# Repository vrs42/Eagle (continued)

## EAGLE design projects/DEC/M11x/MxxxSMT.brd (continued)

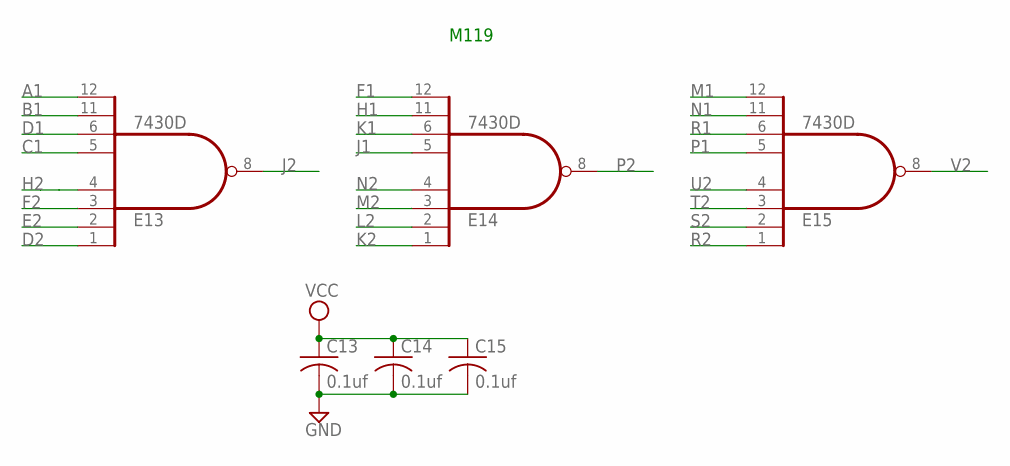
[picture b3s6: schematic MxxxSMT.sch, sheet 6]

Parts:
C13, C14, C15: 0.1uf; C050-025X075
E13, E14, E15: 7430D; SO14

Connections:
A1: E13.12 (I7); also elsewhere on the board
B1: E13.11 (I6); also elsewhere on the board
C1: E13.5 (I4); also elsewhere on the board
D1: E13.6 (I5); also elsewhere on the board
D2: E13.1 (I0); also elsewhere on the board
E2: E13.2 (I1); also elsewhere on the board
F1: E14.12 (I7); also elsewhere on the board
F2: E13.3 (I2); also elsewhere on the board
GND: C13.2, C14.2, C15.2, E13.7 (GND), E14.7 (GND), E15.7 (GND); also elsewhere on the board
H1: E14.11 (I6); also elsewhere on the board
H2: E13.4 (I3); also elsewhere on the board
J1: E14.5 (I4); also elsewhere on the board
J2: E13.8 (O); also elsewhere on the board
K1: E14.6 (I5); also elsewhere on the board
K2: E14.1 (I0); also elsewhere on the board
L2: E14.2 (I1); also elsewhere on the board
M1: E15.12 (I7); also elsewhere on the board
M2: E14.3 (I2); also elsewhere on the board
N1: E15.11 (I6); also elsewhere on the board
N2: E14.4 (I3); also elsewhere on the board
P1: E15.5 (I4); also elsewhere on the board
P2: E14.8 (O); also elsewhere on the board
R1: E15.6 (I5); also elsewhere on the board
R2: E15.1 (I0); also elsewhere on the board
S2: E15.2 (I1); also elsewhere on the board
T2: E15.3 (I2); also elsewhere on the board
U2: E15.4 (I3); also elsewhere on the board
V2: E15.8 (O); also elsewhere on the board
VCC: C13.1, C14.1, C15.1, E13.14 (VCC), E14.14 (VCC), E15.14 (VCC); also elsewhere on the board

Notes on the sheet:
M119

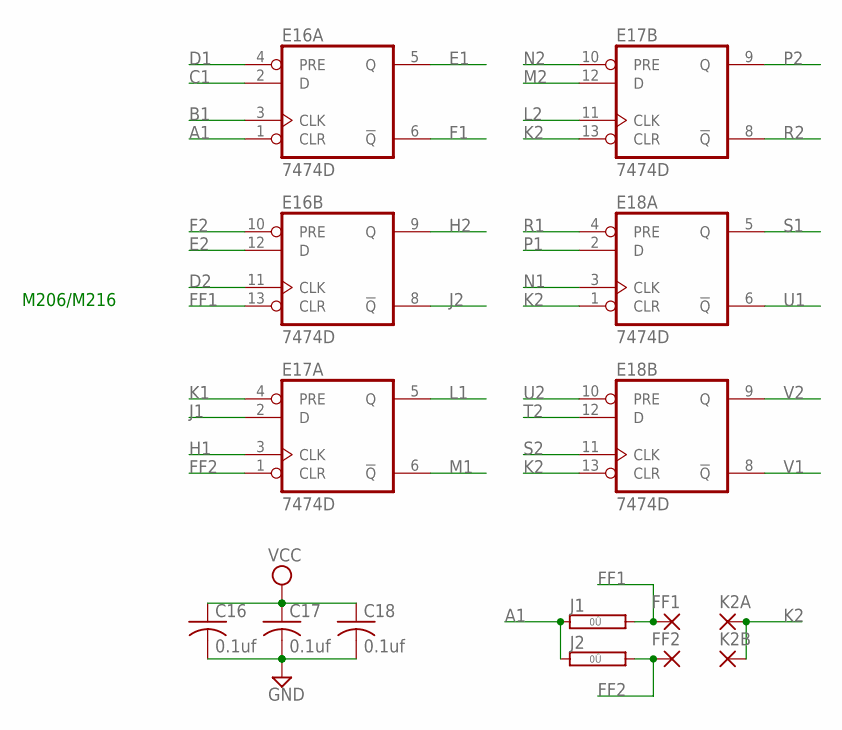
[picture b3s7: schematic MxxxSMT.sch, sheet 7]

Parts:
C16, C17, C18: 0.1uf; C050-025X075
E16, E17, E18: 7474D; SO14
FF1, FF2: 1,6/0,8
J1, J2: 0R; 0R/10
K2A, K2B: 1,6/0,8

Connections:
A1: E16.1 (CLR), J1.1, J2.1; also elsewhere on the board
B1: E16.3 (CLK); also elsewhere on the board
C1: E16.2 (D); also elsewhere on the board
D1: E16.4 (PRE); also elsewhere on the board
D2: E16.11 (CLK); also elsewhere on the board
E1: E16.5 (Q); also elsewhere on the board
E2: E16.12 (D); also elsewhere on the board
F1: E16.6 (!Q); also elsewhere on the board
F2: E16.10 (PRE); also elsewhere on the board
FF1: E16.13 (CLR), FF1.1, J1.2; also elsewhere on the board
FF2: E17.1 (CLR), FF2.1, J2.2; also elsewhere on the board
GND: C16.2, C17.2, C18.2, E16.7 (GND), E17.7 (GND), E18.7 (GND); also elsewhere on the board
H1: E17.3 (CLK); also elsewhere on the board
H2: E16.9 (Q); also elsewhere on the board
J1: E17.2 (D); also elsewhere on the board
J2: E16.8 (!Q); also elsewhere on the board
K1: E17.4 (PRE); also elsewhere on the board
K2: E17.13 (CLR), E18.1 (CLR), E18.13 (CLR), K2A.1, K2B.1; also elsewhere on the board
L1: E17.5 (Q); also elsewhere on the board
L2: E17.11 (CLK); also elsewhere on the board
M1: E17.6 (!Q); also elsewhere on the board
M2: E17.12 (D); also elsewhere on the board
N1: E18.3 (CLK); also elsewhere on the board
N2: E17.10 (PRE); also elsewhere on the board
P1: E18.2 (D); also elsewhere on the board
P2: E17.9 (Q); also elsewhere on the board
R1: E18.4 (PRE); also elsewhere on the board
R2: E17.8 (!Q); also elsewhere on the board
S1: E18.5 (Q); also elsewhere on the board
S2: E18.11 (CLK); also elsewhere on the board
T2: E18.12 (D); also elsewhere on the board
U1: E18.6 (!Q); also elsewhere on the board
U2: E18.10 (PRE); also elsewhere on the board
V1: E18.8 (!Q); also elsewhere on the board
V2: E18.9 (Q); also elsewhere on the board
VCC: C16.1, C17.1, C18.1, E16.14 (VCC), E17.14 (VCC), E18.14 (VCC); also elsewhere on the board

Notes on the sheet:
M206/M216

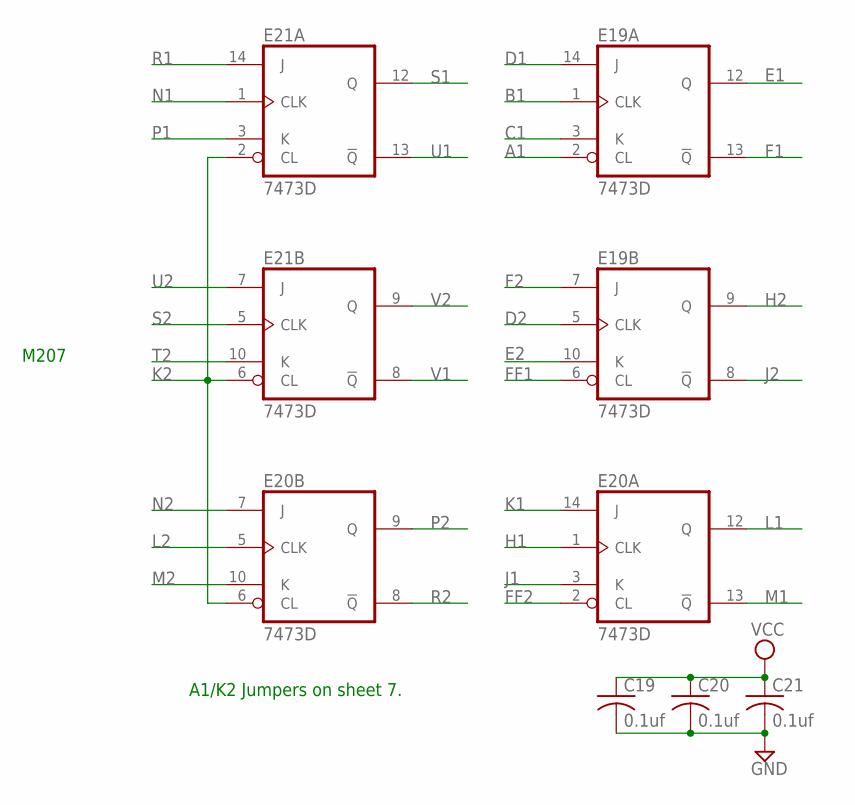
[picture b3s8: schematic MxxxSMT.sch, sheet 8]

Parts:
C19, C20, C21: 0.1uf; C050-025X075
E19, E20, E21: 7473D; SO14

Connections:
A1: E19.2 (CL); also elsewhere on the board
B1: E19.1 (CLK); also elsewhere on the board
C1: E19.3 (K); also elsewhere on the board
D1: E19.14 (J); also elsewhere on the board
D2: E19.5 (CLK); also elsewhere on the board
E1: E19.12 (Q); also elsewhere on the board
E2: E19.10 (K); also elsewhere on the board
F1: E19.13 (!Q); also elsewhere on the board
F2: E19.7 (J); also elsewhere on the board
FF1: E19.6 (CL); also elsewhere on the board
FF2: E20.2 (CL); also elsewhere on the board
GND: C19.2, C20.2, C21.2, E19.11 (GND), E20.11 (GND), E21.11 (GND); also elsewhere on the board
H1: E20.1 (CLK); also elsewhere on the board
H2: E19.9 (Q); also elsewhere on the board
J1: E20.3 (K); also elsewhere on the board
J2: E19.8 (!Q); also elsewhere on the board
K1: E20.14 (J); also elsewhere on the board
K2: E20.6 (CL), E21.2 (CL), E21.6 (CL); also elsewhere on the board
L1: E20.12 (Q); also elsewhere on the board
L2: E20.5 (CLK); also elsewhere on the board
M1: E20.13 (!Q); also elsewhere on the board
M2: E20.10 (K); also elsewhere on the board
N1: E21.1 (CLK); also elsewhere on the board
N2: E20.7 (J); also elsewhere on the board
P1: E21.3 (K); also elsewhere on the board
P2: E20.9 (Q); also elsewhere on the board
R1: E21.14 (J); also elsewhere on the board
R2: E20.8 (!Q); also elsewhere on the board
S1: E21.12 (Q); also elsewhere on the board
S2: E21.5 (CLK); also elsewhere on the board
T2: E21.10 (K); also elsewhere on the board
U1: E21.13 (!Q); also elsewhere on the board
U2: E21.7 (J); also elsewhere on the board
V1: E21.8 (!Q); also elsewhere on the board
V2: E21.9 (Q); also elsewhere on the board
VCC: C19.1, C20.1, C21.1, E19.4 (VCC), E20.4 (VCC), E21.4 (VCC); also elsewhere on the board

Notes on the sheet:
A1/K2 Jumpers on sheet 7.
M207

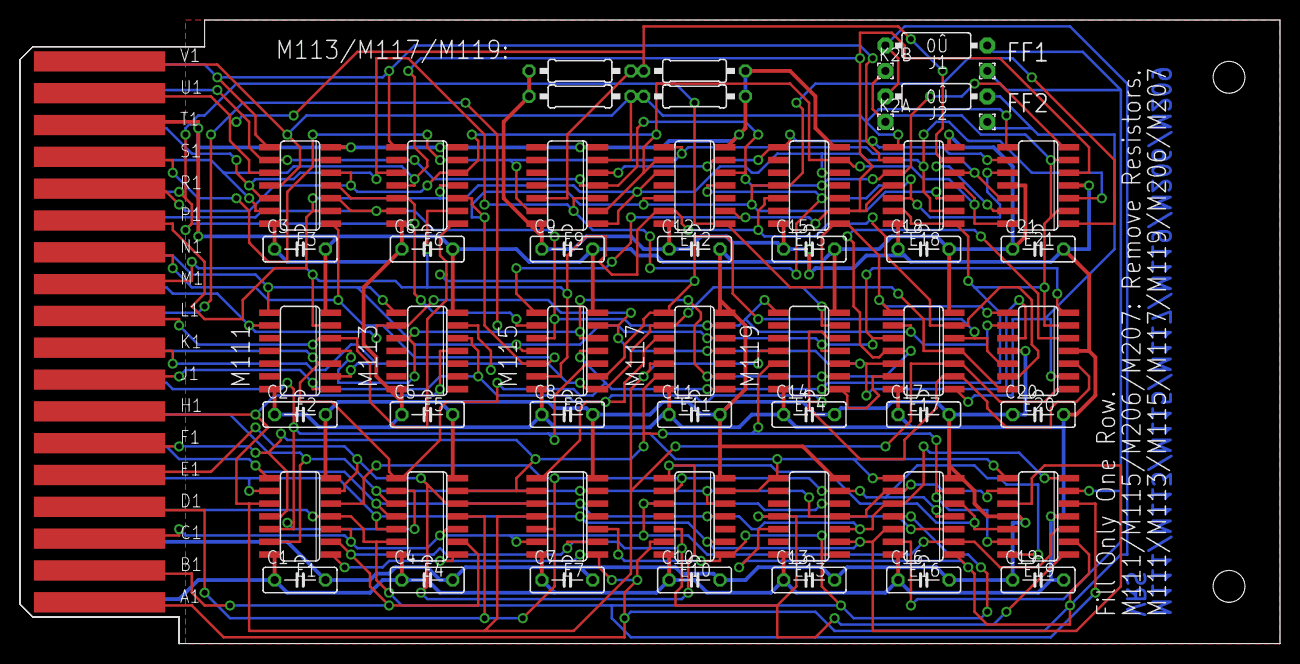
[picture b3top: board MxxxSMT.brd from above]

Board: 2 copper layers, 125.7 x 62.2 mm, 54 parts (0 on the bottom side), 36 nets.

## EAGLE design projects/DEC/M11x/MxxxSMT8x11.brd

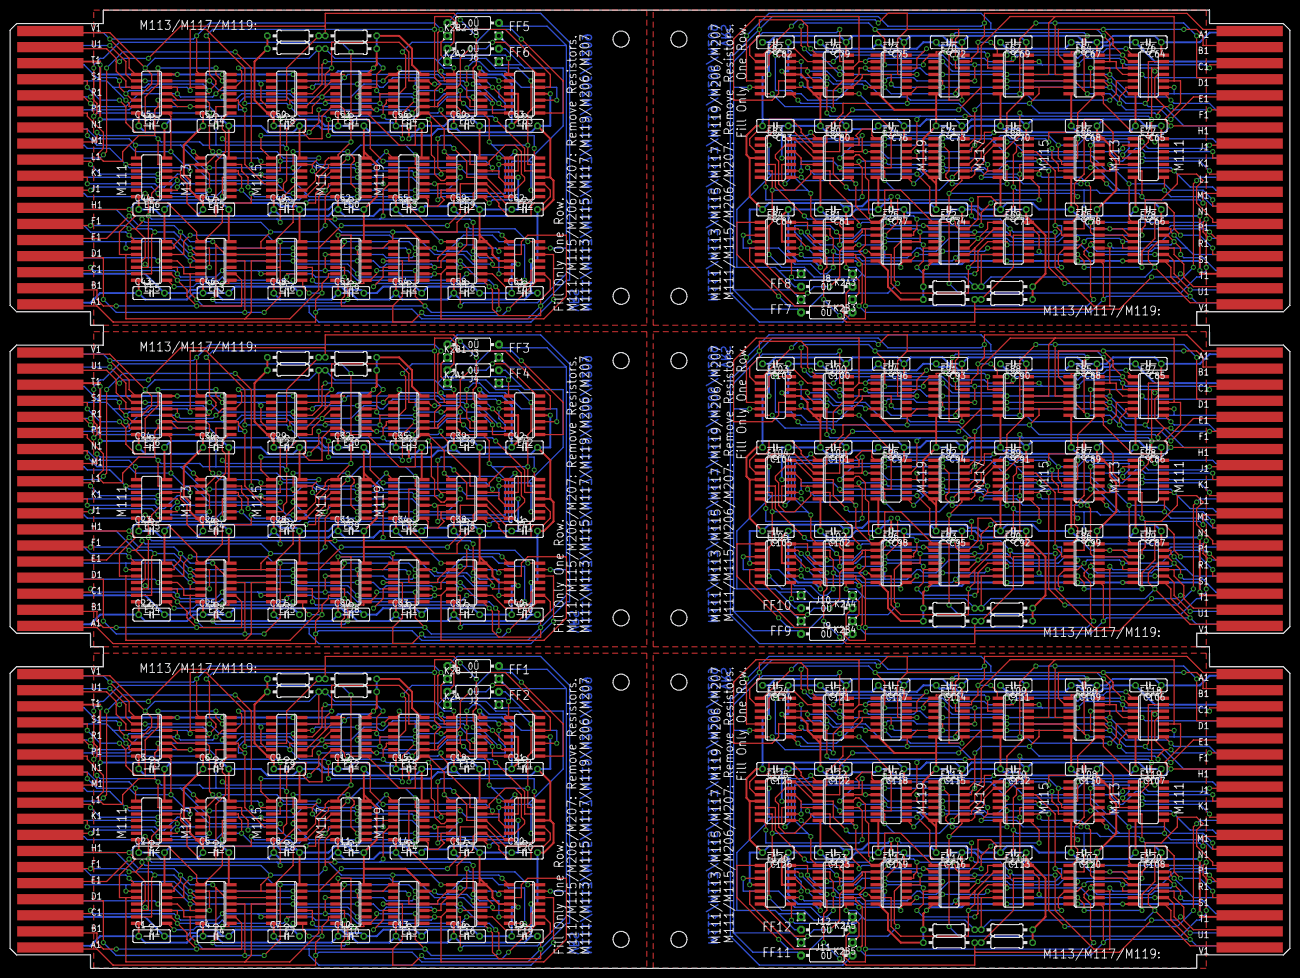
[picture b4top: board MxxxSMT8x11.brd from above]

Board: 2 copper layers, 252.7 x 189.2 mm, 318 parts (0 on the bottom side), 216 nets.

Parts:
C1, C2, C3, C4, C5, C6, C7, C8, C9, C10, C11, C12, C13, C14, C15, C16, C17, C18, C19, C20, C21, C22, C23, C24, C25, C26, C27, C28, C29, C30, C31, C32, C33, C34, C35, C36, C37, C38, C39, C40, C41, C42, C43, C44, C45, C46, C47, C48, C49, C50, C51, C52, C53, C54, C55, C56, C57, C58, C59, C60, C61, C62, C63, C64, C65, C66, C67, C68, C69, C70, C71, C72, C73, C74, C75, C76, C77, C78, C79, C80, C81, C82, C83, C84, C85, C86, C87, C88, C89, C90, C91, C92, C93, C94, C95, C96, C97, C98, C99, C100, C101, C102, C103, C104, C105, C106, C107, C108, C109, C110, C111, C112, C113, C114, C115, C116, C117, C118, C119, C120, C121, C122, C123, C124, C125, C126: 0.1uf; C050-025X075
E1, E2, E3, E34, E35, E36, E55, E56, E57, E76, E77, E78, E97, E98, E99, E118, E119, E120: 7404D; SO14
E4, E5, E6, E22, E23, E24, E43, E44, E45, E64, E65, E66, E85, E86, E87, E106, E107, E108: 7400D; SO14
E7, E8, E9, E25, E26, E27, E46, E47, E48, E67, E68, E69, E88, E89, E90, E109, E110, E111: 7410D; SO14
E10, E11, E12, E28, E29, E30, E49, E50, E51, E70, E71, E72, E91, E92, E93, E112, E113, E114: 7420D; SO14
E13, E14, E15, E31, E32, E33, E52, E53, E54, E73, E74, E75, E94, E95, E96, E115, E116, E117: 7430D; SO14
E16, E17, E18, E37, E38, E39, E58, E59, E60, E79, E80, E81, E100, E101, E102, E121, E122, E123: 7474D; SO14
E19, E20, E21, E40, E41, E42, E61, E62, E63, E82, E83, E84, E103, E104, E105, E124, E125, E126: 7473D; SO14
FF1, FF2, FF3, FF4, FF5, FF6, FF7, FF8, FF9, FF10, FF11, FF12: 1,6/0,8
J1, J2, J3, J4, J5, J6, J7, J8, J9, J10, J11, J12: 0R/10
K2A, K2A1, K2A2, K2A3, K2A4, K2A5, K2B, K2B1, K2B2, K2B3, K2B4, K2B5: 1,6/0,8
R1, R3, R5, R8, R9, R12, R13, R16, R17, R20, R21, R24: 750; 0207/10
R2, R4, R6, R7, R10, R11, R14, R15, R18, R19, R22, R23: 330; 0207/10
U$1, U$2, U$5, U$7, U$9, U$11: EDGE-CON2

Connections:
A1: E1.1, E4.1, E7.1, E10.13, E13.12, E16.1, E19.2, J1.1, J2.1, U$1.A1
A2: E22.1, E25.1, E28.13, E31.12, E34.1, E37.1, E40.2, J3.1, J4.1, U$2.A1
A3: E43.1, E46.1, E49.13, E52.12, E55.1, E58.1, E61.2, J5.1, J6.1, U$5.A1
A4: E64.1, E67.1, E70.13, E73.12, E76.1, E79.1, E82.2, J7.1, J8.1, U$7.A1
A5: E85.1, E88.1, E91.13, E94.12, E97.1, E100.1, E103.2, J9.1, J10.1, U$9.A1
A6: E106.1, E109.1, E112.13, E115.12, E118.1, E121.1, E124.2, J11.1, J12.1, U$11.A1
B1: E1.2, E4.2, E7.2, E10.12, E13.11, E16.3, E19.1, U$1.B1
B4: E22.2, E25.2, E28.12, E31.11, E34.2, E37.3, E40.1, U$2.B1
B6: E43.2, E46.2, E49.12, E52.11, E55.2, E58.3, E61.1, U$5.B1
B8: E64.2, E67.2, E70.12, E73.11, E76.2, E79.3, E82.1, U$7.B1
B10: E85.2, E88.2, E91.12, E94.11, E97.2, E100.3, E103.1, U$9.B1
B12: E106.2, E109.2, E112.12, E115.11, E118.2, E121.3, E124.1, U$11.B1
C1: E1.3, E4.3, E7.13, E10.10, E13.5, E16.2, E19.3, U$1.C1
C2: E22.3, E25.13, E28.10, E31.5, E34.3, E37.2, E40.3, U$2.C1
C3: E43.3, E46.13, E49.10, E52.5, E55.3, E58.2, E61.3, U$5.C1
C4: E64.3, E67.13, E70.10, E73.5, E76.3, E79.2, E82.3, U$7.C1
C5: E85.3, E88.13, E91.10, E94.5, E97.3, E100.2, E103.3, U$9.C1
C6: E106.3, E109.13, E112.10, E115.5, E118.3, E121.2, E124.3, U$11.C1
D1: E1.5, E4.4, E7.12, E10.9, E13.6, E16.4, E19.14, U$1.D1
D2: E1.4, E4.13, E7.3, E10.1, E13.1, E16.11, E19.5, U$1.D2
D3: E22.13, E25.3, E28.1, E31.1, E34.4, E37.11, E40.5, U$2.D2
D4: E22.4, E25.12, E28.9, E31.6, E34.5, E37.4, E40.14, U$2.D1
D5: E43.13, E46.3, E49.1, E52.1, E55.4, E58.11, E61.5, U$5.D2
D6: E43.4, E46.12, E49.9, E52.6, E55.5, E58.4, E61.14, U$5.D1
D7: E64.13, E67.3, E70.1, E73.1, E76.4, E79.11, E82.5, U$7.D2
D8: E64.4, E67.12, E70.9, E73.6, E76.5, E79.4, E82.14, U$7.D1
D9: E85.13, E88.3, E91.1, E94.1, E97.4, E100.11, E103.5, U$9.D2
D10: E85.4, E88.12, E91.9, E94.6, E97.5, E100.4, E103.14, U$9.D1
D11: E106.13, E109.3, E112.1, E115.1, E118.4, E121.11, E124.5, U$11.D2
D12: E106.4, E109.12, E112.9, E115.6, E118.5, E121.4, E124.14, U$11.D1
E1: E1.6, E4.5, E7.10, E10.8, E16.5, E19.12, U$1.E1
E2: E1.9, E4.12, E7.4, E10.2, E13.2, E16.12, E19.10, U$1.E2
E3: E22.12, E25.4, E28.2, E31.2, E34.9, E37.12, E40.10, U$2.E2
E4: E22.5, E25.10, E28.8, E34.6, E37.5, E40.12, U$2.E1
E5: E43.12, E46.4, E49.2, E52.2, E55.9, E58.12, E61.10, U$5.E2
E6: E43.5, E46.10, E49.8, E55.6, E58.5, E61.12, U$5.E1
E7: E64.12, E67.4, E70.2, E73.2, E76.9, E79.12, E82.10, U$7.E2
E8: E64.5, E67.10, E70.8, E76.6, E79.5, E82.12, U$7.E1
E9: E85.12, E88.4, E91.2, E94.2, E97.9, E100.12, E103.10, U$9.E2
E10: E85.5, E88.10, E91.8, E97.6, E100.5, E103.12, U$9.E1
E11: E106.12, E109.4, E112.2, E115.2, E118.9, E121.12, E124.10, U$11.E2
E12: E106.5, E109.10, E112.8, E118.6, E121.5, E124.12, U$11.E1
F1: E1.11, E4.6, E7.9, E11.13, E14.12, E16.6, E19.13, U$1.F1
F2: E1.8, E4.11, E7.5, E10.4, E13.3, E16.10, E19.7, U$1.F2
F3: E22.11, E25.5, E28.4, E31.3, E34.8, E37.10, E40.7, U$2.F2
F4: E22.6, E25.9, E29.13, E32.12, E34.11, E37.6, E40.13, U$2.F1
F5: E43.11, E46.5, E49.4, E52.3, E55.8, E58.10, E61.7, U$5.F2
F6: E43.6, E46.9, E50.13, E53.12, E55.11, E58.6, E61.13, U$5.F1
F7: E64.11, E67.5, E70.4, E73.3, E76.8, E79.10, E82.7, U$7.F2
F8: E64.6, E67.9, E71.13, E74.12, E76.11, E79.6, E82.13, U$7.F1
F9: E85.11, E88.5, E91.4, E94.3, E97.8, E100.10, E103.7, U$9.F2
F10: E85.6, E88.9, E92.13, E95.12, E97.11, E100.6, E103.13, U$9.F1
F11: E106.11, E109.5, E112.4, E115.3, E118.8, E121.10, E124.7, U$11.F2
F12: E106.6, E109.9, E113.13, E116.12, E118.11, E121.6, E124.13, U$11.F1
FF1: E16.13, E19.6, FF1.1, J1.2
FF2: E17.1, E20.2, FF2.1, J2.2
FF3: E37.13, E40.6, FF3.1, J3.2
FF4: E38.1, E41.2, FF4.1, J4.2
FF5: E58.13, E61.6, FF5.1, J5.2
FF6: E59.1, E62.2, FF6.1, J6.2
FF7: E79.13, E82.6, FF7.1, J7.2
FF8: E80.1, E83.2, FF8.1, J8.2
FF9: E100.13, E103.6, FF9.1, J9.2
FF10: E101.1, E104.2, FF10.1, J10.2
FF11: E121.13, E124.6, FF11.1, J11.2
FF12: E122.1, E125.2, FF12.1, J12.2
GND: C1.2, C2.2, C3.2, C4.2, C5.2, C6.2, C7.2, C8.2, C9.2, C10.2, C11.2, C12.2, C13.2, C14.2, C15.2, C16.2, C17.2, C18.2, C19.2, C20.2, C21.2, E1.7, E2.7, E3.7, E4.7, E5.7, E6.7, E7.7, E8.7, E9.7, E10.7, E11.7, E12.7, E13.7, E14.7, E15.7, E16.7, E17.7, E18.7, E19.11, E20.11, E21.11, R1.1, R3.1, U$1.C2, U$1.T1
GND1: C22.2, C23.2, C24.2, C25.2, C26.2, C27.2, C28.2, C29.2, C30.2, C31.2, C32.2, C33.2, C34.2, C35.2, C36.2, C37.2, C38.2, C39.2, C40.2, C41.2, C42.2, E22.7, E23.7, E24.7, E25.7, E26.7, E27.7, E28.7, E29.7, E30.7, E31.7, E32.7, E33.7, E34.7, E35.7, E36.7, E37.7, E38.7, E39.7, E40.11, E41.11, E42.11, R5.1, R8.1, U$2.C2, U$2.T1
GND2: C43.2, C44.2, C45.2, C46.2, C47.2, C48.2, C49.2, C50.2, C51.2, C52.2, C53.2, C54.2, C55.2, C56.2, C57.2, C58.2, C59.2, C60.2, C61.2, C62.2, C63.2, E43.7, E44.7, E45.7, E46.7, E47.7, E48.7, E49.7, E50.7, E51.7, E52.7, E53.7, E54.7, E55.7, E56.7, E57.7, E58.7, E59.7, E60.7, E61.11, E62.11, E63.11, R9.1, R12.1, U$5.C2, U$5.T1
GND3: C64.2, C65.2, C66.2, C67.2, C68.2, C69.2, C70.2, C71.2, C72.2, C73.2, C74.2, C75.2, C76.2, C77.2, C78.2, C79.2, C80.2, C81.2, C82.2, C83.2, C84.2, E64.7, E65.7, E66.7, E67.7, E68.7, E69.7, E70.7, E71.7, E72.7, E73.7, E74.7, E75.7, E76.7, E77.7, E78.7, E79.7, E80.7, E81.7, E82.11, E83.11, E84.11, R13.1, R16.1, U$7.C2, U$7.T1
GND4: C85.2, C86.2, C87.2, C88.2, C89.2, C90.2, C91.2, C92.2, C93.2, C94.2, C95.2, C96.2, C97.2, C98.2, C99.2, C100.2, C101.2, C102.2, C103.2, C104.2, C105.2, E85.7, E86.7, E87.7, E88.7, E89.7, E90.7, E91.7, E92.7, E93.7, E94.7, E95.7, E96.7, E97.7, E98.7, E99.7, E100.7, E101.7, E102.7, E103.11, E104.11, E105.11, R17.1, R20.1, U$9.C2, U$9.T1
GND5: C106.2, C107.2, C108.2, C109.2, C110.2, C111.2, C112.2, C113.2, C114.2, C115.2, C116.2, C117.2, C118.2, C119.2, C120.2, C121.2, C122.2, C123.2, C124.2, C125.2, C126.2, E106.7, E107.7, E108.7, E109.7, E110.7, E111.7, E112.7, E113.7, E114.7, E115.7, E116.7, E117.7, E118.7, E119.7, E120.7, E121.7, E122.7, E123.7, E124.11, E125.11, E126.11, R21.1, R24.1, U$11.C2, U$11.T1
H1: E1.10, E5.4, E7.11, E11.12, E14.11, E17.3, E20.1, U$1.H1
H2: E1.13, E4.10, E7.6, E10.5, E13.4, E16.9, E19.9, U$1.H2
H3: E22.10, E25.6, E28.5, E31.4, E34.13, E37.9, E40.9, U$2.H2
H4: E24.4, E25.11, E29.12, E32.11, E34.10, E38.3, E41.1, U$2.H1
H5: E43.10, E46.6, E49.5, E52.4, E55.13, E58.9, E61.9, U$5.H2
H6: E45.4, E46.11, E50.12, E53.11, E55.10, E59.3, E62.1, U$5.H1
H7: E64.10, E67.6, E70.5, E73.4, E76.13, E79.9, E82.9, U$7.H2
H8: E66.4, E67.11, E71.12, E74.11, E76.10, E80.3, E83.1, U$7.H1
H9: E85.10, E88.6, E91.5, E94.4, E97.13, E100.9, E103.9, U$9.H2
H10: E87.4, E88.11, E92.12, E95.11, E97.10, E101.3, E104.1, U$9.H1
H11: E106.10, E109.6, E112.5, E115.4, E118.13, E121.9, E124.9, U$11.H2
H12: E108.4, E109.11, E113.12, E116.11, E118.10, E122.3, E125.1, U$11.H1
J1: E2.1, E5.5, E7.8, E11.10, E14.5, E17.2, E20.3, U$1.J1
J2: E1.12, E4.9, E8.3, E10.6, E13.8, E16.8, E19.8, U$1.J2
J3: E22.9, E26.3, E28.6, E31.8, E34.12, E37.8, E40.8, U$2.J2
J4: E24.5, E25.8, E29.10, E32.5, E35.1, E38.2, E41.3, U$2.J1
J5: E43.9, E47.3, E49.6, E52.8, E55.12, E58.8, E61.8, U$5.J2
J6: E45.5, E46.8, E50.10, E53.5, E56.1, E59.2, E62.3, U$5.J1
J7: E64.9, E68.3, E70.6, E73.8, E76.12, E79.8, E82.8, U$7.J2
J8: E66.5, E67.8, E71.10, E74.5, E77.1, E80.2, E83.3, U$7.J1
J9: E85.9, E89.3, E91.6, E94.8, E97.12, E100.8, E103.8, U$9.J2
J10: E87.5, E88.8, E92.10, E95.5, E98.1, E101.2, E104.3, U$9.J1
J11: E106.9, E110.3, E112.6, E115.8, E118.12, E121.8, E124.8, U$11.J2
J12: E108.5, E109.8, E113.10, E116.5, E119.1, E122.2, E125.3, U$11.J1
K1: E2.2, E5.6, E8.1, E11.9, E14.6, E17.4, E20.14, U$1.K1
K2: E2.3, E4.8, E8.4, E11.1, E14.1, E17.13, E18.1, E18.13, E20.6, E21.2, E21.6, K2A.1, K2B.1, U$1.K2
K3: E22.8, E26.4, E29.1, E32.1, E35.3, E38.13, E39.1, E39.13, E41.6, E42.2, E42.6, K2A1.1, K2B1.1, U$2.K2
K4: E24.6, E26.1, E29.9, E32.6, E35.2, E38.4, E41.14, U$2.K1
K5: E43.8, E47.4, E50.1, E53.1, E56.3, E59.13, E60.1, E60.13, E62.6, E63.2, E63.6, K2A2.1, K2B2.1, U$5.K2
K6: E45.6, E47.1, E50.9, E53.6, E56.2, E59.4, E62.14, U$5.K1
K7: E64.8, E68.4, E71.1, E74.1, E77.3, E80.13, E81.1, E81.13, E83.6, E84.2, E84.6, K2A3.1, K2B3.1, U$7.K2
K8: E66.6, E68.1, E71.9, E74.6, E77.2, E80.4, E83.14, U$7.K1
K9: E85.8, E89.4, E92.1, E95.1, E98.3, E101.13, E102.1, E102.13, E104.6, E105.2, E105.6, K2A4.1, K2B4.1, U$9.K2
K10: E87.6, E89.1, E92.9, E95.6, E98.2, E101.4, E104.14, U$9.K1
K11: E106.8, E110.4, E113.1, E116.1, E119.3, E122.13, E123.1, E123.13, E125.6, E126.2, E126.6, K2A5.1, K2B5.1, U$11.K2
K12: E108.6, E110.1, E113.9, E116.6, E119.2, E122.4, E125.14, U$11.K1
L1: E2.5, E6.1, E8.2, E11.8, E17.5, E20.12, U$1.L1
L2: E2.4, E5.10, E8.5, E11.2, E14.2, E17.11, E20.5, U$1.L2
L3: E24.10, E26.5, E29.2, E32.2, E35.4, E38.11, E41.5, U$2.L2
L4: E23.1, E26.2, E29.8, E35.5, E38.5, E41.12, U$2.L1
L5: E45.10, E47.5, E50.2, E53.2, E56.4, E59.11, E62.5, U$5.L2
L6: E44.1, E47.2, E50.8, E56.5, E59.5, E62.12, U$5.L1
L7: E66.10, E68.5, E71.2, E74.2, E77.4, E80.11, E83.5, U$7.L2
L8: E65.1, E68.2, E71.8, E77.5, E80.5, E83.12, U$7.L1
L9: E87.10, E89.5, E92.2, E95.2, E98.4, E101.11, E104.5, U$9.L2
L10: E86.1, E89.2, E92.8, E98.5, E101.5, E104.12, U$9.L1
L11: E108.10, E110.5, E113.2, E116.2, E119.4, E122.11, E125.5, U$11.L2
L12: E107.1, E110.2, E113.8, E119.5, E122.5, E125.12, U$11.L1
M1: E2.6, E6.2, E8.13, E12.13, E15.12, E17.6, E20.13, U$1.M1
M2: E2.9, E5.9, E8.6, E11.4, E14.3, E17.12, E20.10, U$1.M2
M3: E24.9, E26.6, E29.4, E32.3, E35.9, E38.12, E41.10, U$2.M2
M4: E23.2, E26.13, E30.13, E33.12, E35.6, E38.6, E41.13, U$2.M1
M5: E45.9, E47.6, E50.4, E53.3, E56.9, E59.12, E62.10, U$5.M2
M6: E44.2, E47.13, E51.13, E54.12, E56.6, E59.6, E62.13, U$5.M1
M7: E66.9, E68.6, E71.4, E74.3, E77.9, E80.12, E83.10, U$7.M2
M8: E65.2, E68.13, E72.13, E75.12, E77.6, E80.6, E83.13, U$7.M1
M9: E87.9, E89.6, E92.4, E95.3, E98.9, E101.12, E104.10, U$9.M2
M10: E86.2, E89.13, E93.13, E96.12, E98.6, E101.6, E104.13, U$9.M1
M11: E108.9, E110.6, E113.4, E116.3, E119.9, E122.12, E125.10, U$11.M2
M12: E107.2, E110.13, E114.13, E117.12, E119.6, E122.6, E125.13, U$11.M1
N1: E3.1, E6.3, E8.12, E12.12, E15.11, E18.3, E21.1, U$1.N1
N2: E2.8, E5.8, E8.11, E11.5, E14.4, E17.10, E20.7, U$1.N2
N3: E24.8, E26.11, E29.5, E32.4, E35.8, E38.10, E41.7, U$2.N2
N4: E23.3, E26.12, E30.12, E33.11, E36.1, E39.3, E42.1, U$2.N1
N5: E45.8, E47.11, E50.5, E53.4, E56.8, E59.10, E62.7, U$5.N2
N6: E44.3, E47.12, E51.12, E54.11, E57.1, E60.3, E63.1, U$5.N1
N7: E66.8, E68.11, E71.5, E74.4, E77.8, E80.10, E83.7, U$7.N2
N8: E65.3, E68.12, E72.12, E75.11, E78.1, E81.3, E84.1, U$7.N1
N9: E87.8, E89.11, E92.5, E95.4, E98.8, E101.10, E104.7, U$9.N2
N10: E86.3, E89.12, E93.12, E96.11, E99.1, E102.3, E105.1, U$9.N1
N11: E108.8, E110.11, E113.5, E116.4, E119.8, E122.10, E125.7, U$11.N2
N12: E107.3, E110.12, E114.12, E117.11, E120.1, E123.3, E126.1, U$11.N1
P1: E3.2, E6.4, E9.1, E12.10, E15.5, E18.2, E21.3, U$1.P1
P2: E3.3, E6.13, E8.10, E11.6, E14.8, E17.9, E20.9, U$1.P2
P3: E23.13, E26.10, E29.6, E32.8, E36.3, E38.9, E41.9, U$2.P2
P4: E23.4, E27.1, E30.10, E33.5, E36.2, E39.2, E42.3, U$2.P1
P5: E44.13, E47.10, E50.6, E53.8, E57.3, E59.9, E62.9, U$5.P2
P6: E44.4, E48.1, E51.10, E54.5, E57.2, E60.2, E63.3, U$5.P1
P7: E65.13, E68.10, E71.6, E74.8, E78.3, E80.9, E83.9, U$7.P2
P8: E65.4, E69.1, E72.10, E75.5, E78.2, E81.2, E84.3, U$7.P1
P9: E86.13, E89.10, E92.6, E95.8, E99.3, E101.9, E104.9, U$9.P2
P10: E86.4, E90.1, E93.10, E96.5, E99.2, E102.2, E105.3, U$9.P1
P11: E107.13, E110.10, E113.6, E116.8, E120.3, E122.9, E125.9, U$11.P2
P12: E107.4, E111.1, E114.10, E117.5, E120.2, E123.2, E126.3, U$11.P1
R1: E3.5, E6.5, E9.2, E12.9, E15.6, E18.4, E21.14, U$1.R1
R2: E3.4, E6.12, E8.9, E12.1, E15.1, E17.8, E20.8, U$1.R2
R3: E23.12, E26.9, E30.1, E33.1, E36.4, E38.8, E41.8, U$2.R2
R4: E23.5, E27.2, E30.9, E33.6, E36.5, E39.4, E42.14, U$2.R1
R5: E44.12, E47.9, E51.1, E54.1, E57.4, E59.8, E62.8, U$5.R2
R6: E44.5, E48.2, E51.9, E54.6, E57.5, E60.4, E63.14, U$5.R1
R7: E65.12, E68.9, E72.1, E75.1, E78.4, E80.8, E83.8, U$7.R2
R8: E65.5, E69.2, E72.9, E75.6, E78.5, E81.4, E84.14, U$7.R1
R9: E86.12, E89.9, E93.1, E96.1, E99.4, E101.8, E104.8, U$9.R2
R10: E86.5, E90.2, E93.9, E96.6, E99.5, E102.4, E105.14, U$9.R1
R11: E107.12, E110.9, E114.1, E117.1, E120.4, E122.8, E125.8, U$11.R2
R12: E107.5, E111.2, E114.9, E117.6, E120.5, E123.4, E126.14, U$11.R1
S1: E3.6, E6.6, E9.13, E12.8, E18.5, E21.12, U$1.S1
S2: E3.13, E6.11, E8.8, E12.2, E15.2, E18.11, E21.5, U$1.S2
S3: E23.11, E26.8, E30.2, E33.2, E36.13, E39.11, E42.5, U$2.S2
S4: E23.6, E27.13, E30.8, E36.6, E39.5, E42.12, U$2.S1
S5: E44.11, E47.8, E51.2, E54.2, E57.13, E60.11, E63.5, U$5.S2
S6: E44.6, E48.13, E51.8, E57.6, E60.5, E63.12, U$5.S1
S7: E65.11, E68.8, E72.2, E75.2, E78.13, E81.11, E84.5, U$7.S2
S8: E65.6, E69.13, E72.8, E78.6, E81.5, E84.12, U$7.S1
S9: E86.11, E89.8, E93.2, E96.2, E99.13, E102.11, E105.5, U$9.S2
S10: E86.6, E90.13, E93.8, E99.6, E102.5, E105.12, U$9.S1
S11: E107.11, E110.8, E114.2, E117.2, E120.13, E123.11, E126.5, U$11.S2
S12: E107.6, E111.13, E114.8, E120.6, E123.5, E126.12, U$11.S1
T1: E23.10, E27.3, E30.4, E33.3, E36.12, E39.12, E42.10, U$2.T2
T2: E3.12, E6.10, E9.3, E12.4, E15.3, E18.12, E21.10, U$1.T2
T3: E44.10, E48.3, E51.4, E54.3, E57.12, E60.12, E63.10, U$5.T2
T4: E65.10, E69.3, E72.4, E75.3, E78.12, E81.12, E84.10, U$7.T2
T5: E86.10, E90.3, E93.4, E96.3, E99.12, E102.12, E105.10, U$9.T2
T6: E107.10, E111.3, E114.4, E117.3, E120.12, E123.12, E126.10, U$11.T2
U1: E3.10, E9.12, E18.6, E21.13, R1.2, R2.1, U$1.U1
U2: E3.9, E6.9, E9.4, E12.5, E15.4, E18.10, E21.7, U$1.U2
U3: E23.9, E27.4, E30.5, E33.4, E36.9, E39.10, E42.7, U$2.U2
U4: E27.12, E36.10, E39.6, E42.13, R5.2, R6.1, U$2.U1
U5: E44.9, E48.4, E51.5, E54.4, E57.9, E60.10, E63.7, U$5.U2
U6: E48.12, E57.10, E60.6, E63.13, R9.2, R10.1, U$5.U1
U7: E65.9, E69.4, E72.5, E75.4, E78.9, E81.10, E84.7, U$7.U2
U8: E69.12, E78.10, E81.6, E84.13, R13.2, R14.1, U$7.U1
U9: E86.9, E90.4, E93.5, E96.4, E99.9, E102.10, E105.7, U$9.U2
U10: E90.12, E99.10, E102.6, E105.13, R17.2, R18.1, U$9.U1
U11: E107.9, E111.4, E114.5, E117.4, E120.9, E123.10, E126.7, U$11.U2
U12: E111.12, E120.10, E123.6, E126.13, R21.2, R22.1, U$11.U1
V1: E3.11, E9.6, E18.8, E21.8, R3.2, R4.1, U$1.V1
V2: E3.8, E6.8, E9.5, E12.6, E15.8, E18.9, E21.9, U$1.V2
V3: E27.6, E36.11, E39.8, E42.8, R7.1, R8.2, U$2.V1
V4: E23.8, E27.5, E30.6, E33.8, E36.8, E39.9, E42.9, U$2.V2
V5: E48.6, E57.11, E60.8, E63.8, R11.1, R12.2, U$5.V1
V6: E44.8, E48.5, E51.6, E54.8, E57.8, E60.9, E63.9, U$5.V2
V7: E69.6, E78.11, E81.8, E84.8, R15.1, R16.2, U$7.V1
V8: E65.8, E69.5, E72.6, E75.8, E78.8, E81.9, E84.9, U$7.V2
V9: E90.6, E99.11, E102.8, E105.8, R19.1, R20.2, U$9.V1
V10: E86.8, E90.5, E93.6, E96.8, E99.8, E102.9, E105.9, U$9.V2
V11: E111.6, E120.11, E123.8, E126.8, R23.1, R24.2, U$11.V1
V12: E107.8, E111.5, E114.6, E117.8, E120.8, E123.9, E126.9, U$11.V2
VCC: C1.1, C2.1, C3.1, C4.1, C5.1, C6.1, C7.1, C8.1, C9.1, C10.1, C11.1, C12.1, C13.1, C14.1, C15.1, C16.1, C17.1, C18.1, C19.1, C20.1, C21.1, E1.14, E2.14, E3.14, E4.14, E5.14, E6.14, E7.14, E8.14, E9.14, E10.14, E11.14, E12.14, E13.14, E14.14, E15.14, E16.14, E17.14, E18.14, E19.4, E20.4, E21.4, R2.2, R4.2, U$1.A2
VCC1: C22.1, C23.1, C24.1, C25.1, C26.1, C27.1, C28.1, C29.1, C30.1, C31.1, C32.1, C33.1, C34.1, C35.1, C36.1, C37.1, C38.1, C39.1, C40.1, C41.1, C42.1, E22.14, E23.14, E24.14, E25.14, E26.14, E27.14, E28.14, E29.14, E30.14, E31.14, E32.14, E33.14, E34.14, E35.14, E36.14, E37.14, E38.14, E39.14, E40.4, E41.4, E42.4, R6.2, R7.2, U$2.A2
VCC2: C43.1, C44.1, C45.1, C46.1, C47.1, C48.1, C49.1, C50.1, C51.1, C52.1, C53.1, C54.1, C55.1, C56.1, C57.1, C58.1, C59.1, C60.1, C61.1, C62.1, C63.1, E43.14, E44.14, E45.14, E46.14, E47.14, E48.14, E49.14, E50.14, E51.14, E52.14, E53.14, E54.14, E55.14, E56.14, E57.14, E58.14, E59.14, E60.14, E61.4, E62.4, E63.4, R10.2, R11.2, U$5.A2
VCC3: C64.1, C65.1, C66.1, C67.1, C68.1, C69.1, C70.1, C71.1, C72.1, C73.1, C74.1, C75.1, C76.1, C77.1, C78.1, C79.1, C80.1, C81.1, C82.1, C83.1, C84.1, E64.14, E65.14, E66.14, E67.14, E68.14, E69.14, E70.14, E71.14, E72.14, E73.14, E74.14, E75.14, E76.14, E77.14, E78.14, E79.14, E80.14, E81.14, E82.4, E83.4, E84.4, R14.2, R15.2, U$7.A2
VCC4: C85.1, C86.1, C87.1, C88.1, C89.1, C90.1, C91.1, C92.1, C93.1, C94.1, C95.1, C96.1, C97.1, C98.1, C99.1, C100.1, C101.1, C102.1, C103.1, C104.1, C105.1, E85.14, E86.14, E87.14, E88.14, E89.14, E90.14, E91.14, E92.14, E93.14, E94.14, E95.14, E96.14, E97.14, E98.14, E99.14, E100.14, E101.14, E102.14, E103.4, E104.4, E105.4, R18.2, R19.2, U$9.A2
VCC5: C106.1, C107.1, C108.1, C109.1, C110.1, C111.1, C112.1, C113.1, C114.1, C115.1, C116.1, C117.1, C118.1, C119.1, C120.1, C121.1, C122.1, C123.1, C124.1, C125.1, C126.1, E106.14, E107.14, E108.14, E109.14, E110.14, E111.14, E112.14, E113.14, E114.14, E115.14, E116.14, E117.14, E118.14, E119.14, E120.14, E121.14, E122.14, E123.14, E124.4, E125.4, E126.4, R22.2, R23.2, U$11.A2
